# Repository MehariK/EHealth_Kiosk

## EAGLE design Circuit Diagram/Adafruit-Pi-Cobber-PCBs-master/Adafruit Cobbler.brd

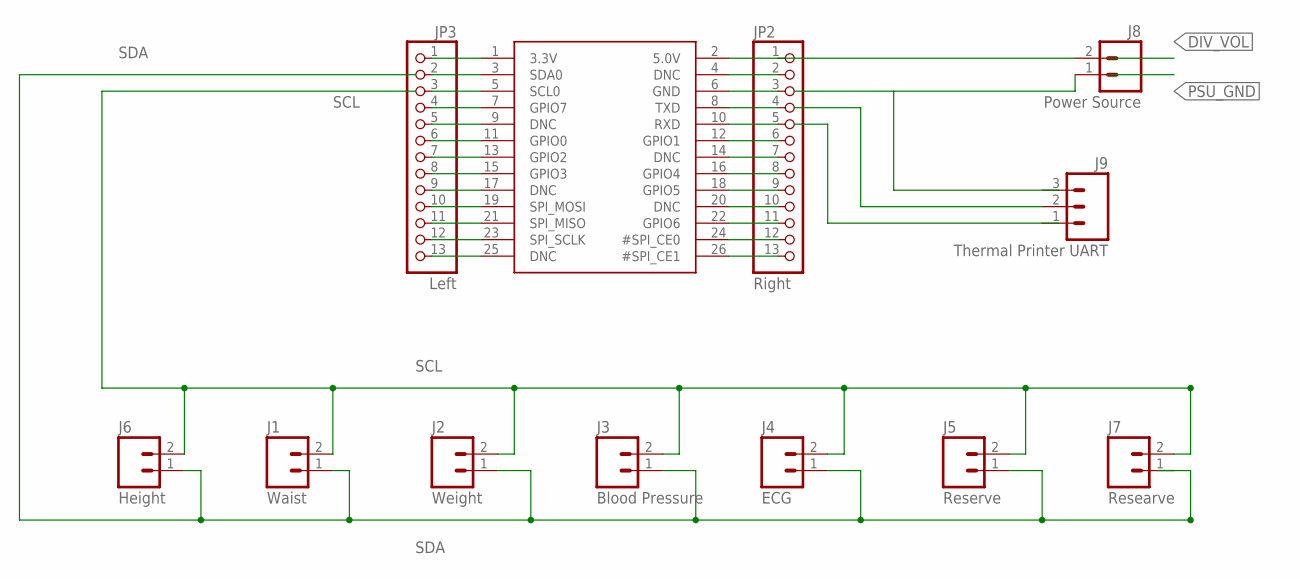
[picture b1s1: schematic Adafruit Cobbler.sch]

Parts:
J1: Waist; JST-2-PTH-KIT
J2: Weight; JST-2-PTH-KIT
J3: Blood Pressure; JST-2-PTH-KIT
J4: ECG; JST-2-PTH-KIT
J5: Reserve; JST-2-PTH-KIT
J6: Height; JST-2-PTH-KIT
J7: Researve; JST-2-PTH-KIT
J8: Power Source; JST-2-PTH-KIT
J9: Thermal Printer UART; JST-3-PTH
JP1: PI; RASBERRYPI_IDC
JP2: Right; 1X13_ROUND_76MIL
JP3: Left; 1X13_ROUND_76MIL

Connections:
3.3V: JP1.1 (3.3V), JP3.1
5.0V: J8.2, JP1.2 (5.0V), JP2.1
GND: JP1.6 (GND), JP2.3
unnamed: JP1.3 (SDA0), JP3.2
unnamed: JP1.5 (SCL0), JP3.3
unnamed: JP1.7 (GPIO7), JP3.4
unnamed: JP1.9 (DNC), JP3.5
unnamed: JP1.11 (GPIO0), JP3.6
unnamed: JP1.13 (GPIO2), JP3.7
unnamed: JP1.15 (GPIO3), JP3.8
unnamed: JP1.17 (DNC), JP3.9
unnamed: JP1.19 (SPI_MOSI), JP3.10
unnamed: JP1.21 (SPI_MISO), JP3.11
unnamed: JP1.23 (SPI_SCLK), JP3.12
unnamed: JP1.25 (DNC), JP3.13
unnamed: JP1.4 (DNC), JP2.2
unnamed: JP1.8 (TXD), JP2.4
unnamed: JP1.10 (RXD), JP2.5
unnamed: JP1.12 (GPIO1), JP2.6
unnamed: JP1.14 (DNC), JP2.7
unnamed: JP1.16 (GPIO4), JP2.8
unnamed: JP1.18 (GPIO5), JP2.9
unnamed: JP1.20 (DNC), JP2.10
unnamed: JP1.22 (GPIO6), JP2.11
unnamed: JP1.24 (#SPI_CE0), JP2.12
unnamed: JP1.26 (#SPI_CE1), JP2.13
SCL: J1.2, J2.2, J3.2, J4.2, J5.2, J6.2, J7.2
SDA: J1.1, J2.1, J3.1, J4.1, J5.1, J6.1

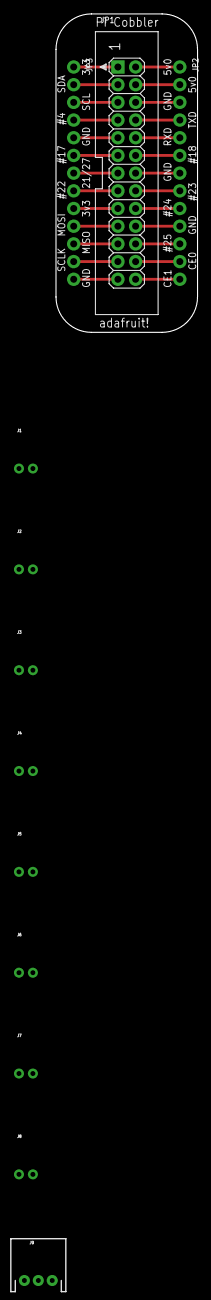
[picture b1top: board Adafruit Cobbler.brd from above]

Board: 2 copper layers, 20.3 x 45.7 mm, 12 parts (0 on the bottom side), 28 nets.

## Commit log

2017-04-25 The first commit for the protype
2017-05-08 Only CS0 on Raspberry Pi is working well at this stage
2017-05-16 GPIO 7 29 31 33 37 has been set as CS on Raspberry Pi and multiple slaves on them run for test
2017-05-17 Work underway on integrating height sensor into the SPI Arduino Raspberry System
2017-05-18 The first modification made to the GPIO33-HEIGHT
2017-05-18 Changes made to variable name in GPIO33-Height
2017-05-18 Updates made to variable name in GPIO33-Height
2017-05-18 Made change to frquency
2017-05-19 Two separate SPI transactions each with spi_end set
2017-05-19 Making changes to the Arduino SPI for Height
2017-05-19 Troubleshooting steps needed for the second part SPI
2017-05-19 The is a problem of criss crossing command and result
2017-05-19 There have been some changes made to the Arduino code to fix criss crossing of command and output
2017-05-20 First working version of the Arduino code for height measurement
2017-05-20 A working version of the height measurement and startup of the weight version
2017-05-29 NIBlood Pressure has Communication Status ok && The design of the Kiosk is also ongoing
2017-06-02 Little progress on HEX ASCII Conversion for the NIBP Reading
2017-06-15 NIBP data read from Arduino
2017-06-15 The first day we read the NIBP measurement data from memory
2017-06-16 Progress on Reading data from BP after mesearment is done
2017-06-19 Blood Pressure Ok and Glucometer Started
2017-06-25 This commit is the working version of the Height
2017-07-03 The first attempt to run SPI command to NIBP
2017-07-05 There is a major change in SPI communication - improved -few more work on receiving NIBP data
2017-07-06 NIBP is now in a good SPI Communicatoin and data reading
2017-07-06 Weight sensor hardware issue has been resolved. There is no software change done
2017-07-07 Introduced average and median calculation to the height measurement
2017-07-07 SPI communication for height has been edited the best workking settings known
2017-07-07 Wight Measurement schetch for is modified with code suitable for SPI communication
2017-07-07 Weigth measurement is updated with average on meassured data
2017-07-07 Updated again with more clarity on SPI communication for height has been edited the best workking settings known
2017-07-07 Oximeter SPI code started with a new location
2017-07-07 Started working respective RPi codes per sesor in each branch
2017-07-08 A new SPI c code for RPi is added file named bcmSPI-CS-GPIO33-Height-test
2017-07-08 Update SPI C code for RPi is added
2017-07-08 The first C code for Oximeter is added
2017-07-08 corrected some typos in the new C code
2017-07-08 edited C code for Waist to run on CS1 for SPI
2017-07-08 edited typo on oximeter GPIO7 C file
2017-07-08 NIBP reading was reduced to Sys, Dia and Pulse. Hence, both Arduino and RPI C code received modificatoins
2017-07-08 Changes made to the order of parameters in *spi_transfernb, and also syia, dia, pulse NIBP readingsl
2017-07-08 Arduino code for NIBP updated with data type for measurement data sis, dia, pulse...
2017-07-08 changed the order of parameters in transfernb file for weight C file
2017-07-10 changes were made to retun data for call with 0xA from RPi and also delay millis to send data to RPi
2017-07-11 0x0F is assigned to valueINp[]
2017-07-13 hex and ascii data exchange over SPI has been corrected...calculation remaining on the RPi side
2017-07-13 RPi version of C file pulled here for edit on hex and ascii part
2017-07-13 Changed made to the RPi* C file now contain calculated value
2017-07-13 Adapted Arduino code to work with real weight measurement data
2017-07-14 This commit has attempts to use the Contec50D+ based on data retrival technique used in MySignal of Cooking-hacks
2017-07-14 Height measurement is updated with floating point expansion
2017-07-18 The firt attemp on using infrared reflective sensor is commited
2017-07-19 Changes were made to the Arduino code of the waist meter. The sensor needs to be changed due to loose connection issue
2017-07-20 updated the caps lock on findIndex function name

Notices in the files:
parts and their libraries:
SparkFun-Connectors: Licensing: Creative Commons ShareAlike 4.0 International - https://creativecommons.org/licenses/by-sa/4.0
